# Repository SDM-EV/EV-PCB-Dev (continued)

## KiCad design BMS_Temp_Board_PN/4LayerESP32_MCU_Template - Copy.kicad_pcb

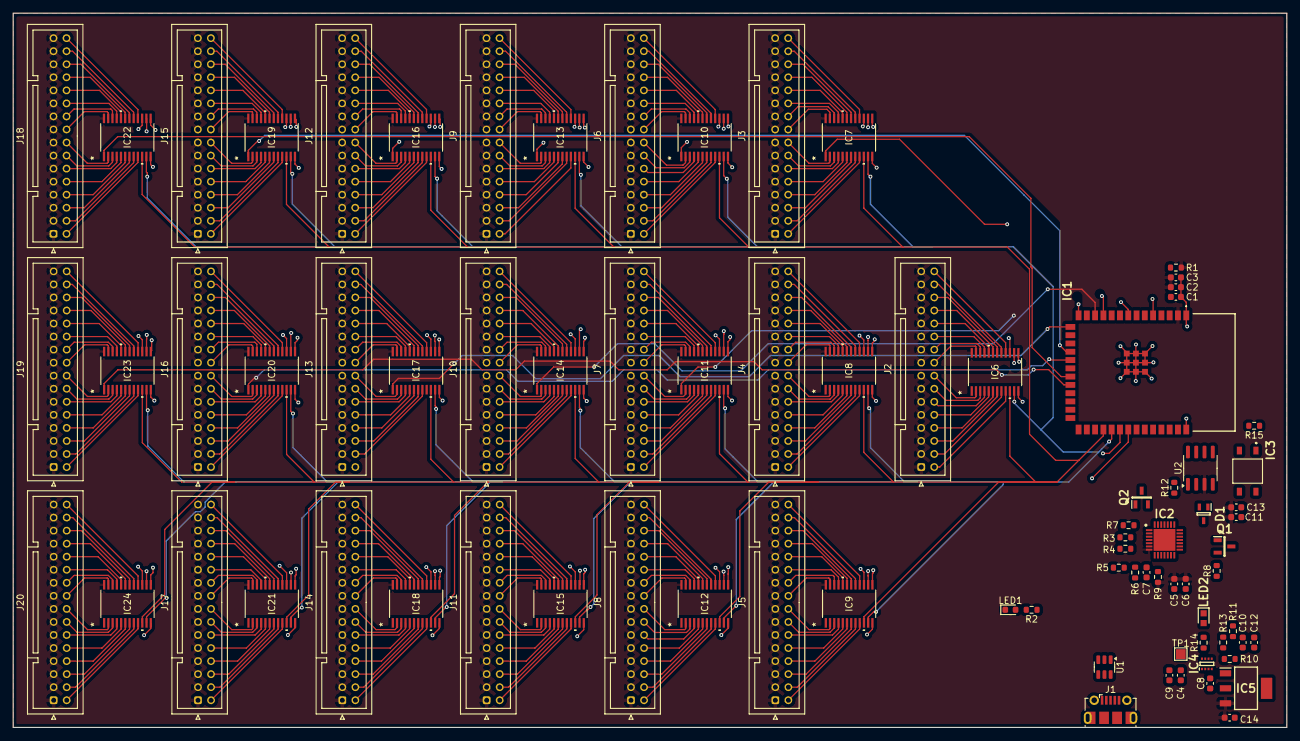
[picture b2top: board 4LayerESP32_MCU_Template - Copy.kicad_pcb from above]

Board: 4 copper layers, 195.2 x 109.5 mm, 81 parts (0 on the bottom side), 360 nets.

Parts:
C1, C4, C7, C8, C9: 1uF; C_0603_1608Metric
C2, C12, C14: 10uF; C_0603_1608Metric
C3, C6, C11, C13: 100nF; C_0603_1608Metric
C5: 4.7uF; C_0603_1608Metric
C10: 100uF; C_0603_1608Metric
D1: ESDCAN03-2BWY; SOT65P210X110-3N
IC1: ESP32-S3-WROOM-1-N8R8; ESP32S3WROOM1N8R8
IC2: CP2102N-A02-GQFN28; QFN50P500X500X80-29N-D
IC3: TLP175A_TPL,E; TLP266J
IC4: TPS2116DRLR; SOTFL50P160X60-8L
IC5: MIC37100-3.3WS; SOT230P700X180-4N
IC6, IC7, IC8, IC9, IC10, IC11, IC12, IC13, IC14, IC15, IC16, IC17, IC18, IC19, IC20, IC21, IC22, IC23, IC24: CD74HC4067PWR; TSSOP24_4P5X7P9_TEX
J1: ESP_USB; USB_Micro-B_Molex-105017-0001
J2, J3, J4, J5, J6, J7, J8, J9, J10, J11, J12, J13, J14, J15, J16, J17, J18, J19, J20: B32B-PUDSS-1_LF__SN_; JST_PUD_B32B-PUDSS_2x16_P2.00mm_Vertical
LED1: GREEN; LED_0603_1608Metric
LED2: 150060RS75000; LEDC1608X80N
Q1, Q2: MMBT2222LT1G; SOT96P237X111-3N
R1, R7, R8, R10, R11, R13, R15: 10k; R_0603_1608Metric
R2: 220; R_0603_1608Metric
R3, R4: 27; R_0603_1608Metric
R5: 22.1K; R_0603_1608Metric
R6: 47.5K; R_0603_1608Metric
R9: 1k; R_0603_1608Metric
R12: 120; R_0603_1608Metric
R14: 68; R_0603_1608Metric
TP1: ST_5V; TestPoint_Pad_1.5x1.5mm
U1: USBLC6-2SC6; SOT-23-6
U2: SN65HVD230; SOIC-8_3.9x4.9mm_P1.27mm

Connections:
+3.3V: C2.2, C3.2, C5.1, C6.2, C11.1, C13.1, C14.2, IC1.2 (3V3), IC2.6 (VDD), IC2.7 (VREGIN), IC5.3 (OUT), IC6.24 (VCC), IC7.24 (VCC), IC8.24 (VCC), IC9.24 (VCC), IC10.24 (VCC), IC11.24 (VCC), IC12.24 (VCC), IC13.24 (VCC), IC14.24 (VCC), IC15.24 (VCC), IC16.24 (VCC), IC17.24 (VCC), IC18.24 (VCC), IC19.24 (VCC), IC20.24 (VCC), IC21.24 (VCC), IC22.24 (VCC), IC23.24 (VCC), IC24.24 (VCC), J2.1, J2.3, J2.5, J2.7, J2.9, J2.11, J2.13, J2.15, J2.17, J2.19, J2.21, J2.23, J2.25, J2.27, J2.29, J2.31, J3.1, J3.3, J3.5, J3.7, J3.9, J3.11, J3.13, J3.15, J3.17, J3.19, J3.21, J3.23, J3.25, J3.27, J3.29, J3.31, J4.1, J4.3, J4.5, J4.7, J4.9, J4.11, J4.13, J4.15, J4.17, J4.19, J4.21, J4.23, J4.25, J4.27, J4.29, J4.31, J5.1, J5.3, J5.5, J5.7, J5.9, J5.11, J5.13, J5.15, J5.17, J5.19, J5.21, J5.23, J5.25, J5.27, J5.29, J5.31, J6.1, J6.3, J6.5, J6.7, J6.9, J6.11, J6.13, J6.15, J6.17, J6.19, J6.21, J6.23, J6.25, J6.27, J6.29, J6.31, J7.1, J7.3, J7.5, J7.7, J7.9, J7.11, J7.13, J7.15, J7.17, J7.19, J7.21, J7.23, J7.25, J7.27, J7.29, J7.31, J8.1, J8.3, J8.5, J8.7, J8.9, J8.11, J8.13, J8.15, J8.17, J8.19, J8.21, J8.23, J8.25, J8.27, J8.29, J8.31, J9.1, J9.3, J9.5, J9.7, J9.9, J9.11, J9.13, J9.15, J9.17, J9.19, J9.21, J9.23, J9.25, J9.27, J9.29, J9.31, J10.1, J10.3, J10.5, J10.7, J10.9, J10.11, J10.13, J10.15, J10.17, J10.19, J10.21, J10.23, J10.25, J10.27, J10.29, J10.31, J11.1, J11.3, J11.5, J11.7, J11.9, J11.11, J11.13, J11.15, J11.17, J11.19, J11.21, J11.23, J11.25, J11.27, J11.29, J11.31, J12.1, J12.3, J12.5, J12.7, J12.9, J12.11, J12.13, J12.15, J12.17, J12.19, J12.21, J12.23, J12.25, J12.27, J12.29, J12.31, J13.1, J13.3, J13.5, J13.7, J13.9, J13.11, J13.13, J13.15, J13.17, J13.19, J13.21, J13.23, J13.25, J13.27, J13.29, J13.31, J14.1, J14.3, J14.5, J14.7, J14.9, J14.11, J14.13, J14.15, J14.17, J14.19, J14.21, J14.23, J14.25, J14.27, J14.29, J14.31, J15.1, J15.3, J15.5, J15.7, J15.9, J15.11, J15.13, J15.15, J15.17, J15.19, J15.21, J15.23, J15.25, J15.27, J15.29, J15.31, J16.1, J16.3, J16.5, J16.7, J16.9, J16.11, J16.13, J16.15, J16.17, J16.19, J16.21, J16.23, J16.25, J16.27, J16.29, J16.31, J17.1, J17.3, J17.5, J17.7, J17.9, J17.11, J17.13, J17.15, J17.17, J17.19, J17.21, J17.23, J17.25, J17.27, J17.29, J17.31, J18.1, J18.3, J18.5, J18.7, J18.9, J18.11, J18.13, J18.15, J18.17, J18.19, J18.21, J18.23, J18.25, J18.27, J18.29, J18.31, J19.1, J19.3, J19.5, J19.7, J19.9, J19.11, J19.13, J19.15, J19.17, J19.19, J19.21, J19.23, J19.25, J19.27, J19.29, J19.31, J20.1, J20.3, J20.5, J20.7, J20.9, J20.11, J20.13, J20.15, J20.17, J20.19, J20.21, J20.23, J20.25, J20.27, J20.29, J20.31, R1.1, R9.2, U2.3 (VCC)
+5V: C10.1, C12.2, IC4.2 (VOUT), IC4.7 (VOUT), IC5.1 (IN), R13.1, R14.1
/CAN+: D1.2, R12.2, U2.7 (CANH)
/CAN-: D1.1, IC3.4, U2.6 (CANL)
/CAN_CTX: IC1.24 (IO47), U2.4 (R)
/CAN_RTX: IC1.25 (IO48), U2.1 (D)
/CAN_TERM: IC1.16 (IO46), IC3.1
/CHIP_PU: C1.1, IC1.3 (EN), R1.2
/GPIO0: IC1.27 (IO0), Q2.3 (C)
/MUX1: IC1.4 (IO4), IC6.1 (COM)
/MUX2: IC1.5 (IO5), IC7.1 (COM)
/MUX3: IC1.6 (IO6), IC8.1 (COM)
/MUX4: IC1.7 (IO7), IC9.1 (COM)
/MUX5: IC1.8 (IO15), IC10.1 (COM)
/MUX6: IC1.9 (IO16), IC11.1 (COM)
/MUX7: IC1.10 (IO17), IC12.1 (COM)
/MUX8: IC1.11 (IO18), IC13.1 (COM)
/MUX9: IC1.12 (IO8), IC14.1 (COM)
/MUX10: IC1.13 (IO19), IC15.1 (COM)
/MUX11: IC1.14 (IO20), IC16.1 (COM)
/MUX12: IC1.15 (IO3), IC17.1 (COM)
/MUX13: IC1.17 (IO9), IC18.1 (COM)
/MUX14: IC1.18 (IO10), IC19.1 (COM)
/MUX15: IC1.19 (IO11), IC20.1 (COM)
/MUX16: IC1.20 (IO12), IC21.1 (COM)
/MUX17: IC1.21 (IO13), IC22.1 (COM)
/MUX18: IC1.22 (IO14), IC23.1 (COM)
/MUX19: IC1.38 (IO2), IC24.1 (COM)
/MUX_S0: IC1.30 (IO37), IC6.10 (S0), IC7.10 (S0), IC8.10 (S0), IC9.10 (S0), IC10.10 (S0), IC11.10 (S0), IC12.10 (S0), IC13.10 (S0), IC14.10 (S0), IC15.10 (S0), IC16.10 (S0), IC17.10 (S0), IC18.10 (S0), IC19.10 (S0), IC20.10 (S0), IC21.10 (S0), IC22.10 (S0), IC23.10 (S0), IC24.10 (S0)
/MUX_S1: IC1.31 (IO38), IC6.11 (S1), IC7.11 (S1), IC8.11 (S1), IC9.11 (S1), IC10.11 (S1), IC11.11 (S1), IC12.11 (S1), IC13.11 (S1), IC14.11 (S1), IC15.11 (S1), IC16.11 (S1), IC17.11 (S1), IC18.11 (S1), IC19.11 (S1), IC20.11 (S1), IC21.11 (S1), IC22.11 (S1), IC23.11 (S1), IC24.11 (S1)
/MUX_S2: IC1.32 (IO39), IC6.14 (S2), IC7.14 (S2), IC8.14 (S2), IC9.14 (S2), IC10.14 (S2), IC11.14 (S2), IC12.14 (S2), IC13.14 (S2), IC14.14 (S2), IC15.14 (S2), IC16.14 (S2), IC17.14 (S2), IC18.14 (S2), IC19.14 (S2), IC20.14 (S2), IC21.14 (S2), IC22.14 (S2), IC23.14 (S2), IC24.14 (S2)
/MUX_S3: IC1.33 (IO40), IC6.13 (S3), IC7.13 (S3), IC8.13 (S3), IC9.13 (S3), IC10.13 (S3), IC11.13 (S3), IC12.13 (S3), IC13.13 (S3), IC14.13 (S3), IC15.13 (S3), IC16.13 (S3), IC17.13 (S3), IC18.13 (S3), IC19.13 (S3), IC20.13 (S3), IC21.13 (S3), IC22.13 (S3), IC23.13 (S3), IC24.13 (S3)
/PROG_D+: IC2.4 (D+), R3.2
/PROG_D-: IC2.5 (D-), R4.1
/PWR_LED: LED2.2 (A), R14.2
/RSTB: IC2.9 (RSTB), R9.1
/ST: IC4.8 (ST), R13.2, TP1.1
/U0RXD: IC1.36 (RXD0), IC2.26 (TXD)
/U0TXD: IC1.37 (TXD0), IC2.25 (RXD)
/USBM_D+: J1.3 (D+), U1.6 (I/O1)
/USBM_D-: J1.2 (D-), U1.4 (I/O2)
/USER_LED: IC1.28 (IO35), R2.1
/USR_LED_RSTR: LED1.2 (A), R2.2
GND: C1.2, C2.1, C3.1, C4.1, C5.2, C6.1, C7.2, C8.1, C9.1, C10.2, C11.2, C12.1, C13.2, C14.1, D1.3, IC1.1 (GND_1), IC1.40 (GND_2), IC1.41 (GND_3), IC1.42 (GND_4), IC1.43 (GND_5), IC1.44 (GND_6), IC1.45 (GND_7), IC1.46 (GND_8), IC1.47 (GND_9), IC1.48 (GND_10), IC1.49 (GND_11), IC2.3 (GND), IC2.29 (BGND), IC3.3, IC4.1 (GND), IC5.2 (GND_1), IC5.4 (GND_2), IC6.12 (GND), IC6.15 (~E), IC7.12 (GND), IC7.15 (~E), IC8.12 (GND), IC8.15 (~E), IC9.12 (GND), IC9.15 (~E), IC10.12 (GND), IC10.15 (~E), IC11.12 (GND), IC11.15 (~E), IC12.12 (GND), IC12.15 (~E), IC13.12 (GND), IC13.15 (~E), IC14.12 (GND), IC14.15 (~E), IC15.12 (GND), IC15.15 (~E), IC16.12 (GND), IC16.15 (~E), IC17.12 (GND), IC17.15 (~E), IC18.12 (GND), IC18.15 (~E), IC19.12 (GND), IC19.15 (~E), IC20.12 (GND), IC20.15 (~E), IC21.12 (GND), IC21.15 (~E), IC22.12 (GND), IC22.15 (~E), IC23.12 (GND), IC23.15 (~E), IC24.12 (GND), IC24.15 (~E), J1.5 (GND), LED1.1 (K), LED2.1 (K), R6.2, R11.1, R15.1, U1.2 (GND), U2.2 (GND)
unnamed: IC2.28 (DTR), Q2.2 (E), R7.2
unnamed: IC2.24 (RTS), Q1.2 (E), R8.2
unnamed: C7.1, IC2.8 (VBUS), R5.1, R6.1
unnamed: IC3.6, R12.1
unnamed: IC4.4 (PR1), R10.1, R11.2
unnamed: IC6.9 (I0), J2.2
unnamed: IC6.8 (I1), J2.4
unnamed: IC6.7 (I2), J2.6
unnamed: IC6.6 (I3), J2.8
unnamed: IC6.5 (I4), J2.10
unnamed: IC6.4 (I5), J2.12
unnamed: IC6.3 (I6), J2.14
unnamed: IC6.2 (I7), J2.16
unnamed: IC6.23 (I8), J2.18
unnamed: IC6.22 (I9), J2.20
unnamed: IC6.21 (I10), J2.22
unnamed: IC6.20 (I11), J2.24
unnamed: IC6.19 (I12), J2.26
unnamed: IC6.18 (I13), J2.28
unnamed: IC6.17 (I14), J2.30
unnamed: IC6.16 (I15), J2.32
unnamed: IC7.9 (I0), J3.2
unnamed: IC7.8 (I1), J3.4
unnamed: IC7.7 (I2), J3.6
unnamed: IC7.6 (I3), J3.8
unnamed: IC7.5 (I4), J3.10
unnamed: IC7.4 (I5), J3.12
unnamed: IC7.3 (I6), J3.14
unnamed: IC7.2 (I7), J3.16
unnamed: IC7.23 (I8), J3.18
unnamed: IC7.22 (I9), J3.20
unnamed: IC7.21 (I10), J3.22
unnamed: IC7.20 (I11), J3.24
unnamed: IC7.19 (I12), J3.26
unnamed: IC7.18 (I13), J3.28
unnamed: IC7.17 (I14), J3.30
unnamed: IC7.16 (I15), J3.32
unnamed: IC8.9 (I0), J4.2
unnamed: IC8.8 (I1), J4.4
unnamed: IC8.7 (I2), J4.6
unnamed: IC8.6 (I3), J4.8
unnamed: IC8.5 (I4), J4.10
unnamed: IC8.4 (I5), J4.12
unnamed: IC8.3 (I6), J4.14
unnamed: IC8.2 (I7), J4.16
unnamed: IC8.23 (I8), J4.18
unnamed: IC8.22 (I9), J4.20
unnamed: IC8.21 (I10), J4.22
unnamed: IC8.20 (I11), J4.24
unnamed: IC8.19 (I12), J4.26
unnamed: IC8.18 (I13), J4.28
unnamed: IC8.17 (I14), J4.30
unnamed: IC8.16 (I15), J4.32
unnamed: IC9.9 (I0), J5.2
unnamed: IC9.8 (I1), J5.4
unnamed: IC9.7 (I2), J5.6
unnamed: IC9.6 (I3), J5.8
unnamed: IC9.5 (I4), J5.10
unnamed: IC9.4 (I5), J5.12
unnamed: IC9.3 (I6), J5.14
unnamed: IC9.2 (I7), J5.16
unnamed: IC9.23 (I8), J5.18
unnamed: IC9.22 (I9), J5.20
unnamed: IC9.21 (I10), J5.22
unnamed: IC9.20 (I11), J5.24
unnamed: IC9.19 (I12), J5.26
unnamed: IC9.18 (I13), J5.28
unnamed: IC9.17 (I14), J5.30
unnamed: IC9.16 (I15), J5.32
unnamed: IC10.9 (I0), J6.2
unnamed: IC10.8 (I1), J6.4
unnamed: IC10.7 (I2), J6.6
unnamed: IC10.6 (I3), J6.8
unnamed: IC10.5 (I4), J6.10
unnamed: IC10.4 (I5), J6.12
unnamed: IC10.3 (I6), J6.14
unnamed: IC10.2 (I7), J6.16
unnamed: IC10.23 (I8), J6.18
unnamed: IC10.22 (I9), J6.20
unnamed: IC10.21 (I10), J6.22
unnamed: IC10.20 (I11), J6.24
unnamed: IC10.19 (I12), J6.26
unnamed: IC10.18 (I13), J6.28
unnamed: IC10.17 (I14), J6.30
unnamed: IC10.16 (I15), J6.32
unnamed: IC11.9 (I0), J7.2
unnamed: IC11.8 (I1), J7.4
unnamed: IC11.7 (I2), J7.6
unnamed: IC11.6 (I3), J7.8
unnamed: IC11.5 (I4), J7.10
unnamed: IC11.4 (I5), J7.12
unnamed: IC11.3 (I6), J7.14
unnamed: IC11.2 (I7), J7.16
unnamed: IC11.23 (I8), J7.18
unnamed: IC11.22 (I9), J7.20
unnamed: IC11.21 (I10), J7.22
unnamed: IC11.20 (I11), J7.24
unnamed: IC11.19 (I12), J7.26
unnamed: IC11.18 (I13), J7.28
unnamed: IC11.17 (I14), J7.30
unnamed: IC11.16 (I15), J7.32
unnamed: IC12.9 (I0), J8.2
unnamed: IC12.8 (I1), J8.4
unnamed: IC12.7 (I2), J8.6
unnamed: IC12.6 (I3), J8.8
unnamed: IC12.5 (I4), J8.10
unnamed: IC12.4 (I5), J8.12
unnamed: IC12.3 (I6), J8.14
unnamed: IC12.2 (I7), J8.16
unnamed: IC12.23 (I8), J8.18
unnamed: IC12.22 (I9), J8.20
unnamed: IC12.21 (I10), J8.22
unnamed: IC12.20 (I11), J8.24
unnamed: IC12.19 (I12), J8.26
unnamed: IC12.18 (I13), J8.28
unnamed: IC12.17 (I14), J8.30
unnamed: IC12.16 (I15), J8.32
unnamed: IC13.9 (I0), J9.2
unnamed: IC13.8 (I1), J9.4
unnamed: IC13.7 (I2), J9.6
unnamed: IC13.6 (I3), J9.8
unnamed: IC13.5 (I4), J9.10
unnamed: IC13.4 (I5), J9.12
unnamed: IC13.3 (I6), J9.14
unnamed: IC13.2 (I7), J9.16
unnamed: IC13.23 (I8), J9.18
unnamed: IC13.22 (I9), J9.20
unnamed: IC13.21 (I10), J9.22
unnamed: IC13.20 (I11), J9.24
unnamed: IC13.19 (I12), J9.26
unnamed: IC13.18 (I13), J9.28
unnamed: IC13.17 (I14), J9.30
unnamed: IC13.16 (I15), J9.32
unnamed: IC14.9 (I0), J10.2
unnamed: IC14.8 (I1), J10.4
unnamed: IC14.7 (I2), J10.6
unnamed: IC14.6 (I3), J10.8
unnamed: IC14.5 (I4), J10.10
unnamed: IC14.4 (I5), J10.12
unnamed: IC14.3 (I6), J10.14
unnamed: IC14.2 (I7), J10.16
unnamed: IC14.23 (I8), J10.18
unnamed: IC14.22 (I9), J10.20
unnamed: IC14.21 (I10), J10.22
unnamed: IC14.20 (I11), J10.24
unnamed: IC14.19 (I12), J10.26
unnamed: IC14.18 (I13), J10.28
unnamed: IC14.17 (I14), J10.30
unnamed: IC14.16 (I15), J10.32
unnamed: IC15.9 (I0), J11.2
unnamed: IC15.8 (I1), J11.4
unnamed: IC15.7 (I2), J11.6
unnamed: IC15.6 (I3), J11.8
unnamed: IC15.5 (I4), J11.10
unnamed: IC15.4 (I5), J11.12
unnamed: IC15.3 (I6), J11.14
unnamed: IC15.2 (I7), J11.16
unnamed: IC15.23 (I8), J11.18
unnamed: IC15.22 (I9), J11.20
unnamed: IC15.21 (I10), J11.22
unnamed: IC15.20 (I11), J11.24
unnamed: IC15.19 (I12), J11.26
unnamed: IC15.18 (I13), J11.28
unnamed: IC15.17 (I14), J11.30
unnamed: IC15.16 (I15), J11.32
unnamed: IC16.9 (I0), J12.2
unnamed: IC16.8 (I1), J12.4
unnamed: IC16.7 (I2), J12.6
unnamed: IC16.6 (I3), J12.8
unnamed: IC16.5 (I4), J12.10
unnamed: IC16.4 (I5), J12.12
unnamed: IC16.3 (I6), J12.14
unnamed: IC16.2 (I7), J12.16
unnamed: IC16.23 (I8), J12.18
unnamed: IC16.22 (I9), J12.20
unnamed: IC16.21 (I10), J12.22
unnamed: IC16.20 (I11), J12.24
unnamed: IC16.19 (I12), J12.26
unnamed: IC16.18 (I13), J12.28
unnamed: IC16.17 (I14), J12.30
unnamed: IC16.16 (I15), J12.32
unnamed: IC17.9 (I0), J13.2
unnamed: IC17.8 (I1), J13.4
unnamed: IC17.7 (I2), J13.6
unnamed: IC17.6 (I3), J13.8
unnamed: IC17.5 (I4), J13.10
unnamed: IC17.4 (I5), J13.12
unnamed: IC17.3 (I6), J13.14
unnamed: IC17.2 (I7), J13.16
unnamed: IC17.23 (I8), J13.18
unnamed: IC17.22 (I9), J13.20
unnamed: IC17.21 (I10), J13.22
unnamed: IC17.20 (I11), J13.24
unnamed: IC17.19 (I12), J13.26
unnamed: IC17.18 (I13), J13.28
unnamed: IC17.17 (I14), J13.30
unnamed: IC17.16 (I15), J13.32
unnamed: IC18.9 (I0), J14.2
unnamed: IC18.8 (I1), J14.4
unnamed: IC18.7 (I2), J14.6
unnamed: IC18.6 (I3), J14.8
unnamed: IC18.5 (I4), J14.10
unnamed: IC18.4 (I5), J14.12
unnamed: IC18.3 (I6), J14.14
unnamed: IC18.2 (I7), J14.16
unnamed: IC18.23 (I8), J14.18
unnamed: IC18.22 (I9), J14.20
unnamed: IC18.21 (I10), J14.22
unnamed: IC18.20 (I11), J14.24
unnamed: IC18.19 (I12), J14.26
unnamed: IC18.18 (I13), J14.28
unnamed: IC18.17 (I14), J14.30
unnamed: IC18.16 (I15), J14.32
unnamed: IC19.9 (I0), J15.2
unnamed: IC19.8 (I1), J15.4
unnamed: IC19.7 (I2), J15.6
unnamed: IC19.6 (I3), J15.8
unnamed: IC19.5 (I4), J15.10
unnamed: IC19.4 (I5), J15.12
unnamed: IC19.3 (I6), J15.14
unnamed: IC19.2 (I7), J15.16
unnamed: IC19.23 (I8), J15.18
unnamed: IC19.22 (I9), J15.20
unnamed: IC19.21 (I10), J15.22
unnamed: IC19.20 (I11), J15.24
unnamed: IC19.19 (I12), J15.26
unnamed: IC19.18 (I13), J15.28
unnamed: IC19.17 (I14), J15.30
unnamed: IC19.16 (I15), J15.32
unnamed: IC20.9 (I0), J16.2
unnamed: IC20.8 (I1), J16.4
unnamed: IC20.7 (I2), J16.6
unnamed: IC20.6 (I3), J16.8
unnamed: IC20.5 (I4), J16.10
unnamed: IC20.4 (I5), J16.12
unnamed: IC20.3 (I6), J16.14
unnamed: IC20.2 (I7), J16.16
unnamed: IC20.23 (I8), J16.18
unnamed: IC20.22 (I9), J16.20
unnamed: IC20.21 (I10), J16.22
unnamed: IC20.20 (I11), J16.24
unnamed: IC20.19 (I12), J16.26
unnamed: IC20.18 (I13), J16.28
unnamed: IC20.17 (I14), J16.30
unnamed: IC20.16 (I15), J16.32
unnamed: IC21.9 (I0), J17.2
unnamed: IC21.8 (I1), J17.4
unnamed: IC21.7 (I2), J17.6
unnamed: IC21.6 (I3), J17.8
unnamed: IC21.5 (I4), J17.10
unnamed: IC21.4 (I5), J17.12
unnamed: IC21.3 (I6), J17.14
unnamed: IC21.2 (I7), J17.16
unnamed: IC21.23 (I8), J17.18
unnamed: IC21.22 (I9), J17.20
unnamed: IC21.21 (I10), J17.22
unnamed: IC21.20 (I11), J17.24
unnamed: IC21.19 (I12), J17.26
unnamed: IC21.18 (I13), J17.28
unnamed: IC21.17 (I14), J17.30
unnamed: IC21.16 (I15), J17.32
unnamed: IC22.9 (I0), J18.2
unnamed: IC22.8 (I1), J18.4
unnamed: IC22.7 (I2), J18.6
unnamed: IC22.6 (I3), J18.8
unnamed: IC22.5 (I4), J18.10
unnamed: IC22.4 (I5), J18.12
unnamed: IC22.3 (I6), J18.14
unnamed: IC22.2 (I7), J18.16
unnamed: IC22.23 (I8), J18.18
unnamed: IC22.22 (I9), J18.20
unnamed: IC22.21 (I10), J18.22
unnamed: IC22.20 (I11), J18.24
unnamed: IC22.19 (I12), J18.26
unnamed: IC22.18 (I13), J18.28
unnamed: IC22.17 (I14), J18.30
unnamed: IC22.16 (I15), J18.32
unnamed: IC23.9 (I0), J19.2
unnamed: IC23.8 (I1), J19.4
unnamed: IC23.7 (I2), J19.6
unnamed: IC23.6 (I3), J19.8
unnamed: IC23.5 (I4), J19.10
unnamed: IC23.4 (I5), J19.12
unnamed: IC23.3 (I6), J19.14
unnamed: IC23.2 (I7), J19.16
unnamed: IC23.23 (I8), J19.18
unnamed: IC23.22 (I9), J19.20
unnamed: IC23.21 (I10), J19.22
unnamed: IC23.20 (I11), J19.24
unnamed: IC23.19 (I12), J19.26
unnamed: IC23.18 (I13), J19.28
unnamed: IC23.17 (I14), J19.30
unnamed: IC23.16 (I15), J19.32
unnamed: IC24.9 (I0), J20.2
unnamed: IC24.8 (I1), J20.4
unnamed: IC24.7 (I2), J20.6
unnamed: IC24.6 (I3), J20.8
unnamed: IC24.5 (I4), J20.10
unnamed: IC24.4 (I5), J20.12
unnamed: IC24.3 (I6), J20.14
unnamed: IC24.2 (I7), J20.16
unnamed: IC24.23 (I8), J20.18
unnamed: IC24.22 (I9), J20.20
unnamed: IC24.21 (I10), J20.22
unnamed: IC24.20 (I11), J20.24
unnamed: IC24.19 (I12), J20.26
unnamed: IC24.18 (I13), J20.28
unnamed: IC24.17 (I14), J20.30
unnamed: IC24.16 (I15), J20.32
unnamed: Q1.1 (B), R7.1
unnamed: Q2.1 (B), R8.1
unnamed: R3.1, U1.1 (I/O1)
unnamed: R4.2, U1.3 (I/O2)
unnamed: R15.2, U2.8 (Rs)
VBUS: C4.2, C9.2, IC4.6 (VIN2), J1.1 (VBUS), R5.2, U1.5 (VBUS)
VCC: C8.2, IC4.3 (VIN1), IC4.5 (MODE), R10.2

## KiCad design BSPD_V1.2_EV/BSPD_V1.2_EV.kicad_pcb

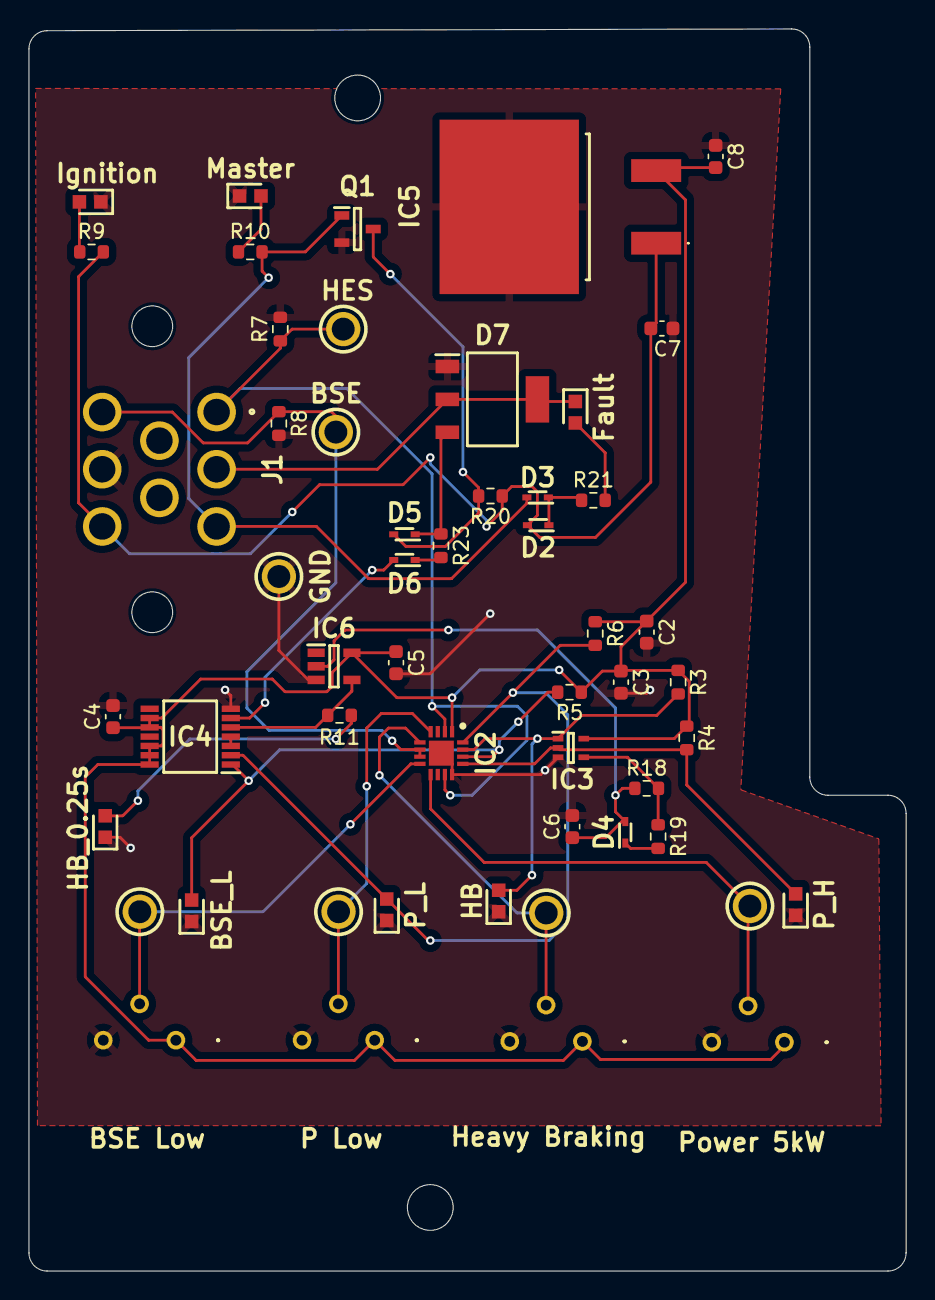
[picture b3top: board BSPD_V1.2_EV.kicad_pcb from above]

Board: 2 copper layers, 61.3 x 86.9 mm, 53 parts (0 on the bottom side), 29 nets.

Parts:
BLACK_TP1: 5006
BSE_L: 150060GS75000; LEDC1608X80N
C2, C3, C4, C5: 1uF; C_0603_1608Metric
C6: 10uF; C_0603_1608Metric
C7: 0.33uF; C_0603_1608Metric
C8: 0.1uF; C_0603_1608Metric
D2, D3, D4, D5, D6: BAT54XV2T1G; SODFL1608X70N
D7: X0202MN_5BA4; SOT230P700X190-4N
Fault: 150060GS75000; LEDC1608X80N
HB: 150060GS75000; LEDC1608X80N
HB_0.25s: 150060GS75000; LEDC1608X80N
IC2: LM2901BIRTER; QFN50P300X300X80-17N-D
IC3: 74AHC1G08; SOT65P212X110-5L
IC4: SN74HC32PWR; SOP65P640X120-14L
IC5: L7805ACD2T-TR; L7805ACD2TTR
IC6: SN74LVC1G17DBVRG4; SOT95P280X145-5N
Ignition: 150060RS75000; LEDC1608X80N
J1: 776280-1
Master: 150060RS75000; LEDC1608X80N
P_H: 150060GS75000; LEDC1608X80N
P_L: 150060GS75000; LEDC1608X80N
Q1: 2N7002,215; SOT95P230X110-3N
R3, R4, R5, R6, R11: 220; R_0603_1608Metric
R7, R8, R20: 10k; R_0603_1608Metric
R9, R10, R21: 510; R_0603_1608Metric
R18: 25k; R_0603_1608Metric
R19: 100; R_0603_1608Metric
R23: 1k; R_0603_1608Metric
RED_TP3, RED_TP4, RED_TP5, RED_TP6: 5005
VR3, VR4, VR5, VR6: 10k; 3386P1103TLF
WHITE_TP1, WHITE_TP2: 5007

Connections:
+5V: C2.1, C3.1, C4.1, C5.1, C8.2, IC2.1 (VCC), IC3.5 (VCC), IC4.9 (3A), IC4.10 (3B), IC4.12 (4A), IC4.13 (4B), IC4.14 (VCC), IC5.3 (OUT), IC6.5 (VCC), R3.1, R4.1, R5.1, R6.1, VR3.1 (CCW), VR4.1 (CCW), VR5.1 (CCW), VR6.1 (CCW)
/12V IGNITION: C7.2, D2.2 (A), IC5.1 (IN), J1.8, R9.2, R20.1
/12V MASTER: D3.2 (A), J1.3, Q1.1 (G), R10.2
/BL+PL_FAULT: IC4.3 (1Y), IC4.4 (2A)
/BSE: IC2.6 (IN2+), IC2.7 (IN3-), J1.6, R8.1, WHITE_TP1.1
/BSE_LOW_FAULT: BSE_L.2 (A), IC2.14 (OUT3), IC4.1 (1A), R5.2
/BSE_LOW_REF: IC2.8 (IN3+), RED_TP6.1, VR6.2 (Wiper)
/BSPD_LOGIC_SIGNAL: D6.2 (A), IC4.6 (2Y)
/HB*5kW_0.25s_FAULT: IC4.5 (2B), IC6.4 (Y), R11.1
/HB*5kW_FAULT: C6.1, D4.2 (A), IC6.2 (A), R18.2
/HEAVY_BRAKING_FAULT: HB.2 (A), IC2.15 (OUT2), IC3.1 (B), R3.2
/HEAVY_BRAKING_REF: IC2.5 (IN2-), RED_TP4.1, VR4.2 (Wiper)
/P_5kW_FAULT: IC2.13 (OUT4), IC3.2 (A), P_H.2 (A), R4.2
/P_HIGH_REF: IC2.9 (IN4-), RED_TP3.1, VR3.2 (Wiper)
/P_LOW_FAULT: IC2.16 (OUT1), IC4.2 (1B), P_L.2 (A), R6.2
/P_LOW_REF: IC2.4 (IN1+), RED_TP5.1, VR5.2 (Wiper)
/P_MAIN: IC2.2 (IN1-), IC2.11 (IN4+), J1.1, R7.1, WHITE_TP2.1
/SCR Gate: D5.1 (K), D7.3 (G), R23.1
BSPD KILL SIGNAL: D7.2 (A_1), D7.4 (A_2), Fault.1 (K), J1.2
GND: BLACK_TP1.1, BSE_L.1 (K), C2.2, C3.2, C4.2, C5.2, C6.2, C7.1, C8.1, D7.1 (K), HB.1 (K), HB_0.25s.1 (K), IC2.12 (GND), IC2.17 (EP), IC3.3 (GND), IC4.7 (GND), IC5.2 (GND), IC6.3 (GND), Ignition.1 (K), J1.7, Master.1 (K), P_H.1 (K), P_L.1 (K), Q1.2 (S), R7.2, R8.2, VR3.3 (CW), VR4.3 (CW), VR5.3 (CW), VR6.3 (CW)
unnamed: D2.1 (K), D3.1 (K), R21.1
unnamed: D4.1 (K), R19.2
unnamed: D5.2 (A), Q1.3 (D), R20.2
unnamed: D6.1 (K), R23.2
unnamed: IC3.4 (Y), R18.1, R19.1
unnamed: Ignition.2 (A), R9.1
unnamed: Master.2 (A), R10.1
unnamed: Fault.2 (A), R21.2
unnamed: HB_0.25s.2 (A), R11.2

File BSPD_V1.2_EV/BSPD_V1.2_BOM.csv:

"Reference","Qty","Value","DNP","Exclude from BOM","Exclude from Board","Footprint","Datasheet"
"BLACK_TP1","1","5006","","","","SDM_MiscFootprint:5006","https://www.keyelco.com/product-pdf.cfm?p=1315"
"C2,C3,C4,C5","4","1uF","","","","Capacitor_SMD:C_0603_1608Metric","~"
"C6","1","10uF","","","","Capacitor_SMD:C_0603_1608Metric","~"
"C7","1","0.33uF","","","","Capacitor_SMD:C_0603_1608Metric","~"
"C8","1","0.1uF","","","","Capacitor_SMD:C_0603_1608Metric","~"
"D2,D3,D4,D5,D6","5","BAT54XV2T1G","","","","SDM_MiscFootprint:SODFL1608X70N","https://www.onsemi.com/pub/Collateral/BAT54XV2T1-D.PDF"
"D7","1","X0202MN_5BA4","","","","SDM_MiscFootprint:SOT230P700X190-4N","http://www.st.com/st-web-ui/static/active/en/resource/techni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"
"IC2","1","LM2901BIRTER","","","","SDM_MiscFootprint:QFN50P300X300X80-17N-D","https://www.ti.com/lit/ds/symlink/lm339b.pdf?ts=174964647414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"
"IC3","1","74AHC1G08","","","","SDM_MiscFootprint:SOT65P212X110-5L","https://assets.nexperia.com/documents/data-sheet/74AHC_AHCT1G08.pdf"
"IC4","1","SN74HC32PWR","","","","SDM_MiscFootprint:SOP65P640X120-14L","http://www.ti.com/lit/gpn/sn74hc32"
"IC5","1","L7805ACD2T-TR","","","","SDM_MiscFootprint:L7805ACD2TTR","https://www.st.com/content/ccc/resource/technical/document/d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"
"IC6","1","SN74LVC1G17DBVRG4","","","","Misc:SOT95P280X145-5N","http://www.ti.com/lit/gpn/SN74LVC1G17"
"J1","1","776280-1","","","","SDM_MiscFootprint:776280-1","https://www.te.com/commerce/DocumentDelivery/DDEController?A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"
"LED1,LED2","2","150060RS75000","","","","SDM_MiscFootprint:LEDC1608X80N","https://www.we-online.com/components/products/datasheet/1500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"
"LED4,LED5,LED6,LED7,LED8,LED9","6","150060GS75000","","","","SDM_MiscFootprint:LEDC1608X80N","https://componentsearchengine.com/Datasheets/2/150060GS75000.pdf"
"Q1","1","2N7002,215","","","","SDM_MiscFootprint:SOT95P230X110-3N","https://assets.nexperia.com/documents/data-sheet/2N7002.pdf"
"R3,R4,R5,R6,R11","5","220","","","","Resistor_SMD:R_0603_1608Metric","~"
"R7,R8,R20","3","10k","","","","Resistor_SMD:R_0603_1608Metric","~"
"R9,R10,R21","3","510","","","","Resistor_SMD:R_0603_1608Metric","~"
"R18","1","25k","","","","Resistor_SMD:R_0603_1608Metric","~"
"R19","1","100","","","","Resistor_SMD:R_0603_1608Metric","~"
"R23","1","1k","","","","Resistor_SMD:R_0603_1608Metric","~"
"RED_TP3,RED_TP4,RED_TP5,RED_TP6","4","5005","","","","SDM_MiscFootprint:5005","http://www.keyelco.com/product-pdf.cfm?p=1314"
"VR3,VR4,VR5,VR6","4","10k","","","","SDM_MiscFootprint:3386P1103TLF","https://www.mouser.com/datasheet/2/54/3386-776606.pdf"
"WHITE_TP1,WHITE_TP2","2","5007","","","","SDM_MiscFootprint:5007","https://www.keyelco.com/product-pdf.cfm?p=1316"

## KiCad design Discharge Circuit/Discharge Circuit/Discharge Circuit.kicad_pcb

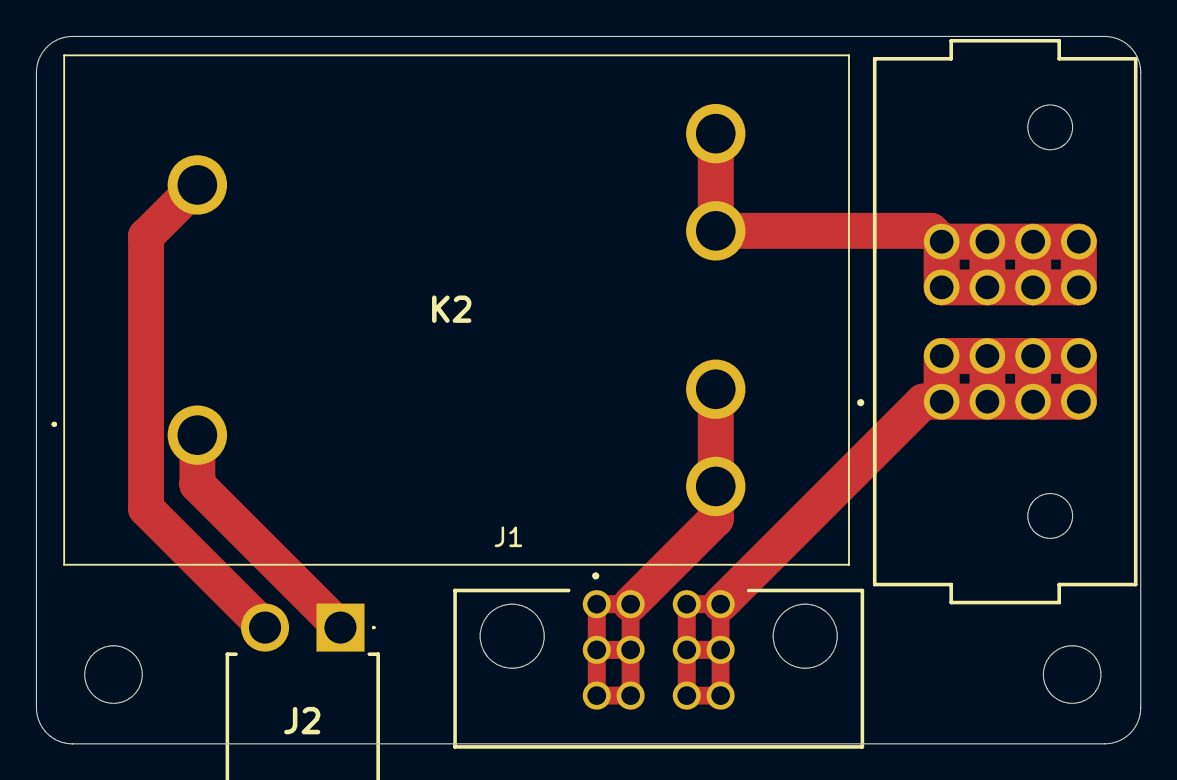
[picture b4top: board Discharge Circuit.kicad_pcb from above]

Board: 2 copper layers, 61.3 x 39.3 mm, 6 parts (0 on the bottom side), 5 nets.

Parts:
H1, H2: MountingHole; MountingHole_3.2mm_M3
J1: MPT-02-01-XX-X-RA-SD; SAMTEC_MPT-02-01-XX-X-RA-SD
J2: IPBT-102-H1-T-S-RA-K; IPBT102H1TSRAK
J3: PET-02-01-T-VT-LC; SAMTEC_PET-02-XX-X-VT-LC
K2: FTR-E1AA012Y-GR; FTRE1AA012YGR

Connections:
GND: J2.2, K2.2 (-)
unnamed: J1.2, J3.1
unnamed: J2.1, K2.1 (+)
unnamed: J1.1, K2.31 (NO_1_1), K2.32 (NO_1_2)
unnamed: J3.2, K2.41 (NO_2_1), K2.42 (NO_2_2)

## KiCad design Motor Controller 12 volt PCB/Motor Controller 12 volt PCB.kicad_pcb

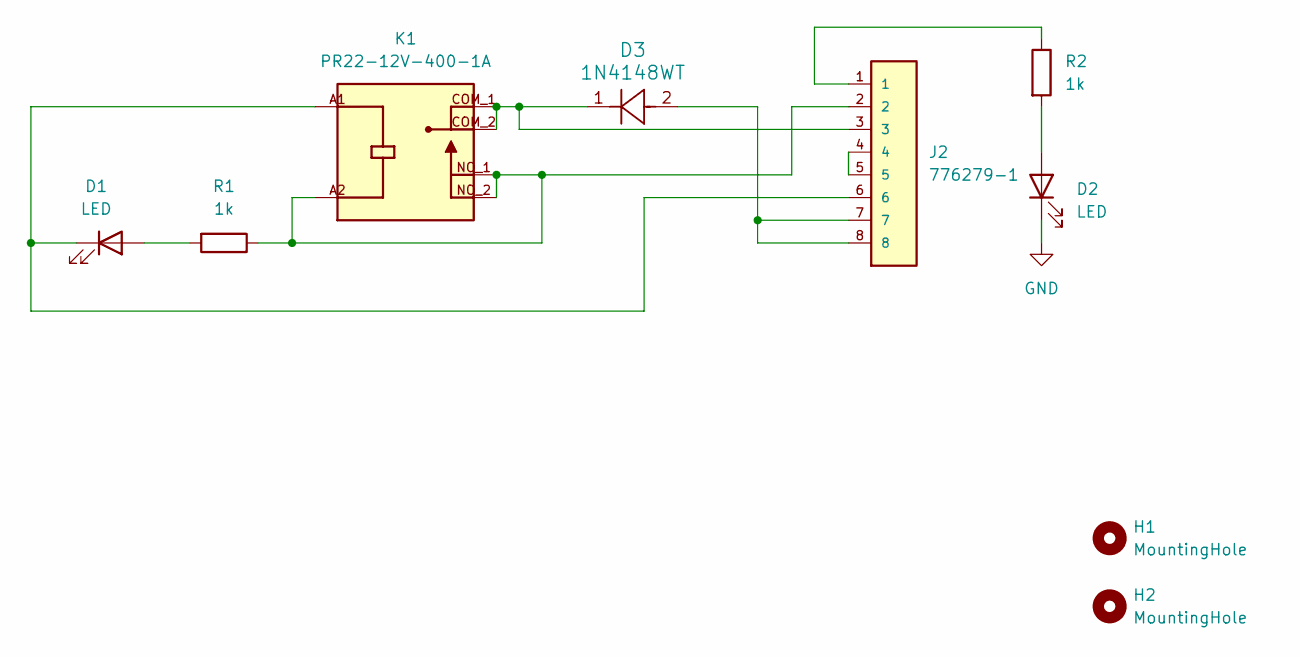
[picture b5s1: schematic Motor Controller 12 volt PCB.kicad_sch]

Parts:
D1, D2: LED; LED_1206_3216Metric
D3: 1N4148WT; D_1206_3216Metric
H1, H2: MountingHole; MountingHole_3.2mm_M3
J2: 776279-1; TE_776279-1; PARTREV F7
K1: PR22-12V-400-1A; RELAY_PR22-12V-400-1A; PARTREV 1.0
R1, R2: 1k; R_1206_3216Metric

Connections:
GND: D2.1 (K)
unnamed: D1.2 (A), R1.2
unnamed: D1.1 (K), J2.6, K1.A1
unnamed: D2.2 (A), R2.2
unnamed: D3.1, J2.3, K1.COM_1, K1.COM_2
unnamed: D3.2, J2.7, J2.8
unnamed: J2.1, R2.1
unnamed: J2.2, K1.A2, K1.NO_1, K1.NO_2, R1.1
unnamed: J2.4, J2.5

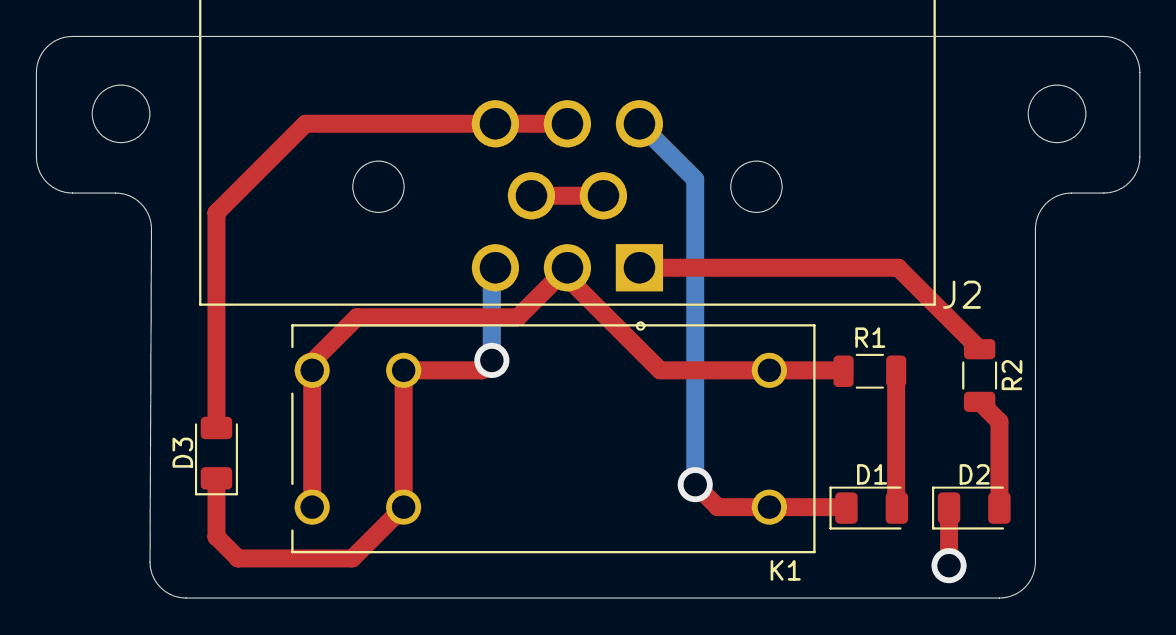
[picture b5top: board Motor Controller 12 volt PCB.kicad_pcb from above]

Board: 2 copper layers, 61.3 x 31.2 mm, 9 parts (0 on the bottom side), 8 nets.
